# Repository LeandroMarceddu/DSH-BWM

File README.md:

# DSH-BWM
# DSH-BetterWaterManager
An attempt to make an RO-water unit a little bit more smart. 

PCB in boards/.

The rest is code.

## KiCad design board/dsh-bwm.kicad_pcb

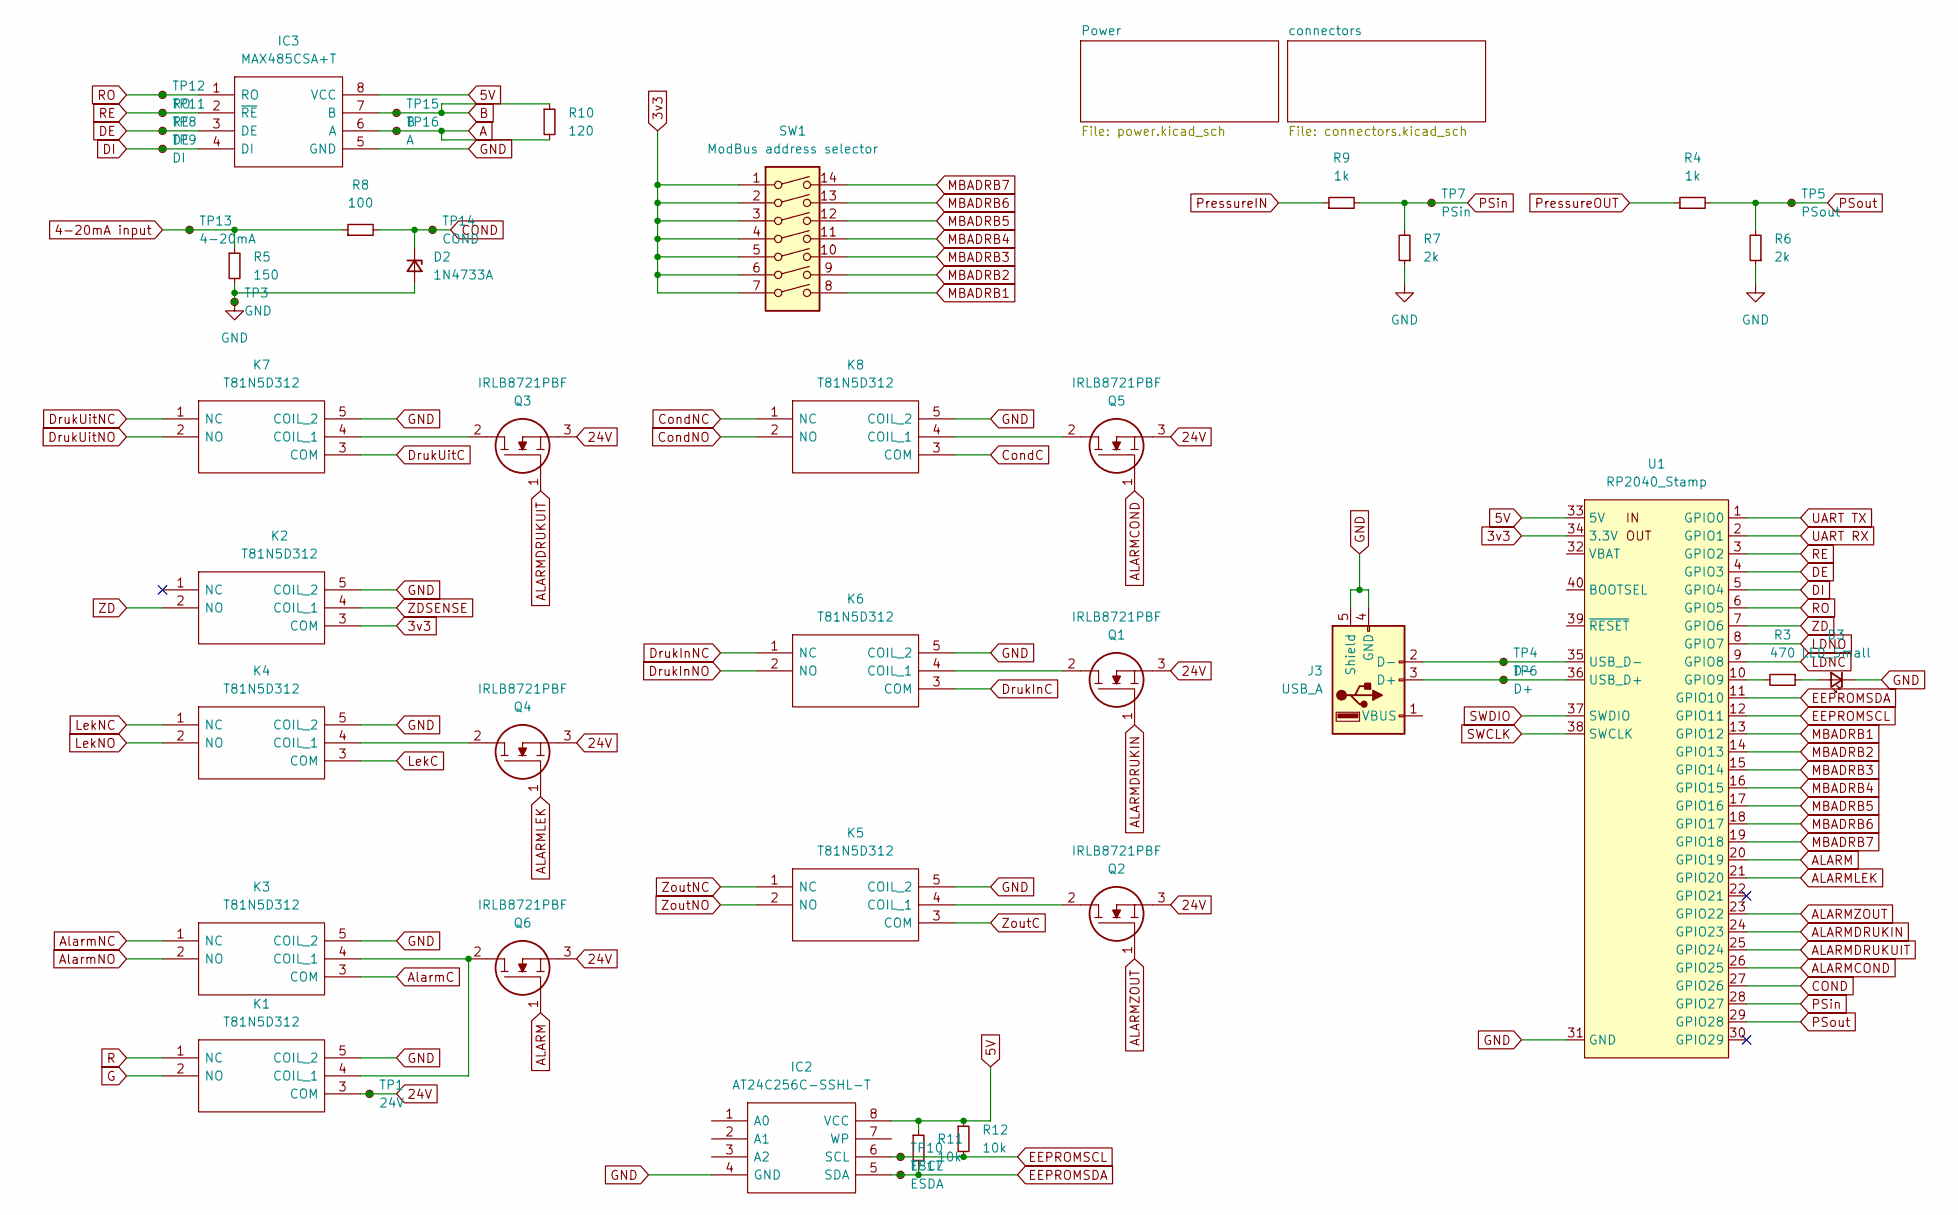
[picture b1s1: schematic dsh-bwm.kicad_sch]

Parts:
D2: 1N4733A; DIOAD1380W86L436D236
D3: LED_Small; LED_0603_1608Metric
IC2: AT24C256C-SSHL-T; SOIC127P600X175-8N; Manufacturer_Part_Number AT24C256C-SSHL-T; Mouser Part Number 556-AT24C256C-SSHL-T
IC3: MAX485CSA+T; SOIC127P600X175-8N; Manufacturer_Part_Number MAX485CSA+T; Mouser Part Number 700-MAX485CSAT
J3: USB_A; USB_A_Molex_105057_Vertical
K1, K2, K3, K4, K5, K6, K7, K8: T81N5D312; T81H5D31212; Manufacturer_Part_Number T81N5D312-05; Mouser Part Number 655-T81N5D312-05
Q1, Q2, Q3, Q4, Q5, Q6: IRLB8721PBF; TO254P483X1016X1994-3P; Manufacturer_Part_Number IRLB8721PBF; Mouser Part Number 942-IRLB8721PBF
R3: 470; R_0805_2012Metric
R4, R9: 1k; R_0805_2012Metric
R5: 150; R_0805_2012Metric; JLC 0402WGF1500TCE
R6, R7: 2k; R_0805_2012Metric
R8: 100; R_0805_2012Metric
R10: 120; R_0805_2012Metric
R11, R12: 10k; R_0805_2012Metric; JLC 0402WGF1500TCE
SW1: ModBus address selector; SW_DIP_SPSTx07_Slide_6.7x19.34mm_W7.62mm_P2.54mm_LowProfile
TP1: 24V; TestPoint_Pad_D1.5mm
TP3: GND; TestPoint_Pad_D1.5mm
TP4: D-; TestPoint_Pad_D1.5mm
TP5: PSout; TestPoint_Pad_D1.5mm
TP6: D+; TestPoint_Pad_D1.5mm
TP7: PSin; TestPoint_Pad_D1.5mm
TP8: DE; TestPoint_Pad_D1.5mm
TP9: DI; TestPoint_Pad_D1.5mm
TP10: ESCL; TestPoint_Pad_D1.5mm
TP11: RE; TestPoint_Pad_D1.5mm
TP12: RO; TestPoint_Pad_D1.5mm
TP13: 4-20mA; TestPoint_Pad_D1.5mm
TP14: COND; TestPoint_Pad_D1.5mm
TP15: B; TestPoint_Pad_D1.5mm
TP16: A; TestPoint_Pad_D1.5mm
TP17: ESDA; TestPoint_Pad_D1.5mm
U1: RP2040_Stamp; RP2040_Stamp_SMD

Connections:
3v3: K2.3 (COM), SW1.1, SW1.2, SW1.3, SW1.4, SW1.5, SW1.6, SW1.7, U1.34 (3.3V); also elsewhere on the board
4-20mA input: R5.1, R8.1, TP13.1; also elsewhere on the board
5V: IC2.8 (VCC), IC3.8 (VCC), R11.1, R12.1, U1.33 (5V); also elsewhere on the board
24V: K1.3 (COM), Q1.3, Q2.3, Q3.3, Q4.3, Q5.3, Q6.3, TP1.1; also elsewhere on the board
A: IC3.6 (A), R10.2, TP16.1; also elsewhere on the board
ALARM: Q6.1, U1.20 (GPIO19)
ALARMCOND: Q5.1, U1.26 (GPIO25)
ALARMDRUKIN: Q1.1, U1.24 (GPIO23)
ALARMDRUKUIT: Q3.1, U1.25 (GPIO24)
ALARMLEK: Q4.1, U1.21 (GPIO20)
ALARMZOUT: Q2.1, U1.23 (GPIO22)
AlarmC: K3.3 (COM); also elsewhere on the board
AlarmNC: K3.1 (NC); also elsewhere on the board
AlarmNO: K3.2 (NO); also elsewhere on the board
B: IC3.7 (B), R10.1, TP15.1; also elsewhere on the board
COND: D2.1 (K), R8.2, TP14.1, U1.27 (GPIO26)
CondC: K8.3 (COM); also elsewhere on the board
CondNC: K8.1 (NC); also elsewhere on the board
CondNO: K8.2 (NO); also elsewhere on the board
DE: IC3.3 (DE), TP8.1, U1.4 (GPIO3)
DI: IC3.4 (DI), TP9.1, U1.5 (GPIO4)
DrukInC: K6.3 (COM); also elsewhere on the board
DrukInNC: K6.1 (NC); also elsewhere on the board
DrukInNO: K6.2 (NO); also elsewhere on the board
DrukUitC: K7.3 (COM); also elsewhere on the board
DrukUitNC: K7.1 (NC); also elsewhere on the board
DrukUitNO: K7.2 (NO); also elsewhere on the board
EEPROMSCL: IC2.6 (SCL), R12.2, TP10.1, U1.12 (GPIO11)
EEPROMSDA: IC2.5 (SDA), R11.2, TP17.1, U1.11 (GPIO10)
G: K1.2 (NO); also elsewhere on the board
GND: D2.2 (A), D3.1 (K), IC2.4 (GND), IC3.5 (GND), J3.4 (GND), J3.5 (Shield), K1.5 (COIL_2), K2.5 (COIL_2), K3.5 (COIL_2), K4.5 (COIL_2), K5.5 (COIL_2), K6.5 (COIL_2), K7.5 (COIL_2), K8.5 (COIL_2), R5.2, R6.1, R7.1, TP3.1, U1.31 (GND); also elsewhere on the board
LDNC: U1.9 (GPIO8); also elsewhere on the board
LDNO: U1.8 (GPIO7); also elsewhere on the board
LekC: K4.3 (COM); also elsewhere on the board
LekNC: K4.1 (NC); also elsewhere on the board
LekNO: K4.2 (NO); also elsewhere on the board
MBADRB1: SW1.8, U1.13 (GPIO12)
MBADRB2: SW1.9, U1.14 (GPIO13)
MBADRB3: SW1.10, U1.15 (GPIO14)
MBADRB4: SW1.11, U1.16 (GPIO15)
MBADRB5: SW1.12, U1.17 (GPIO16)
MBADRB6: SW1.13, U1.18 (GPIO17)
MBADRB7: SW1.14, U1.19 (GPIO18)
unnamed: D3.2 (A), R3.1
unnamed: J3.2 (D-), TP4.1, U1.35 (USB_D-)
unnamed: J3.3 (D+), TP6.1, U1.36 (USB_D+)
unnamed: K1.4 (COIL_1), K3.4 (COIL_1), Q6.2
unnamed: K4.4 (COIL_1), Q4.2
unnamed: K5.4 (COIL_1), Q2.2
unnamed: K6.4 (COIL_1), Q1.2
unnamed: K7.4 (COIL_1), Q3.2
unnamed: K8.4 (COIL_1), Q5.2
unnamed: R3.2, U1.10 (GPIO9)
PSin: R7.2, R9.2, TP7.1, U1.28 (GPIO27)
PSout: R4.2, R6.2, TP5.1, U1.29 (GPIO28)
PressureIN: R9.1; also elsewhere on the board
PressureOUT: R4.1; also elsewhere on the board
R: K1.1 (NC); also elsewhere on the board
RE: IC3.2 (~RE), TP11.1, U1.3 (GPIO2)
RO: IC3.1 (RO), TP12.1, U1.6 (GPIO5)
SWCLK: U1.38 (SWCLK); also elsewhere on the board
SWDIO: U1.37 (SWDIO); also elsewhere on the board
UART RX: U1.2 (GPIO1); also elsewhere on the board
UART TX: U1.1 (GPIO0); also elsewhere on the board
ZD: K2.2 (NO), U1.7 (GPIO6)
ZDSENSE: K2.4 (COIL_1); also elsewhere on the board
ZoutC: K5.3 (COM); also elsewhere on the board
ZoutNC: K5.1 (NC); also elsewhere on the board
ZoutNO: K5.2 (NO); also elsewhere on the board

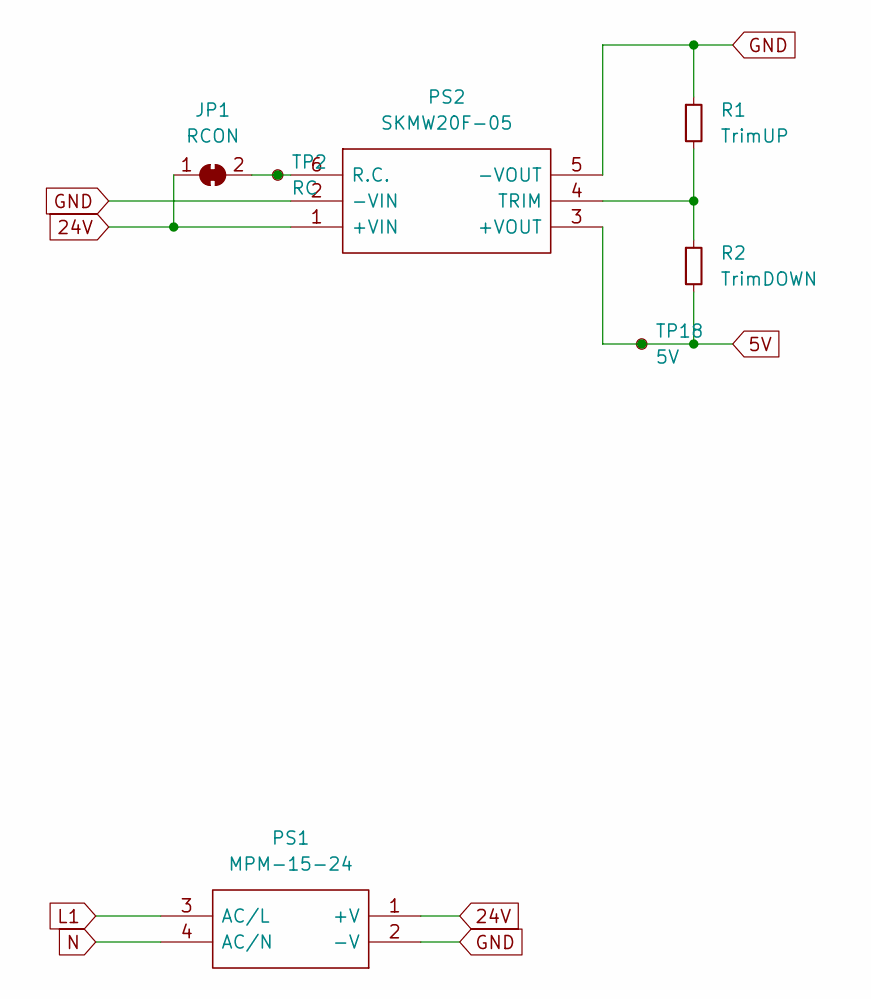
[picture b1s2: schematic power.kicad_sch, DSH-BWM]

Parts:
JP1: RCON; SolderJumper-2_P1.3mm_Open_RoundedPad1.0x1.5mm
PS1: MPM-15-24; MPM1524; Manufacturer_Part_Number MPM-15-24; Mouser Part Number 709-MPM-15-24
PS2: SKMW20F-05; SKMW20F05; Manufacturer_Part_Number SKMW20F-05; Mouser Part Number 709-SKMW20F-05
R1: TrimUP; R_0805_2012Metric
R2: TrimDOWN; R_0805_2012Metric
TP2: RC; TestPoint_Pad_D1.5mm
TP18: 5V; TestPoint_Pad_D1.5mm

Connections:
5V: PS2.3 (+VOUT), R2.2, TP18.1; also elsewhere on the board
24V: JP1.1 (A), PS1.1 (+V), PS2.1 (+VIN); also elsewhere on the board
GND: PS1.2 (-V), PS2.2 (-VIN), PS2.5 (-VOUT), R1.1; also elsewhere on the board
L1: PS1.3 (AC/L); also elsewhere on the board
N: PS1.4 (AC/N); also elsewhere on the board
unnamed: PS2.4 (TRIM), R1.2, R2.1
unnamed: JP1.2 (B), PS2.6 (R.C.), TP2.1

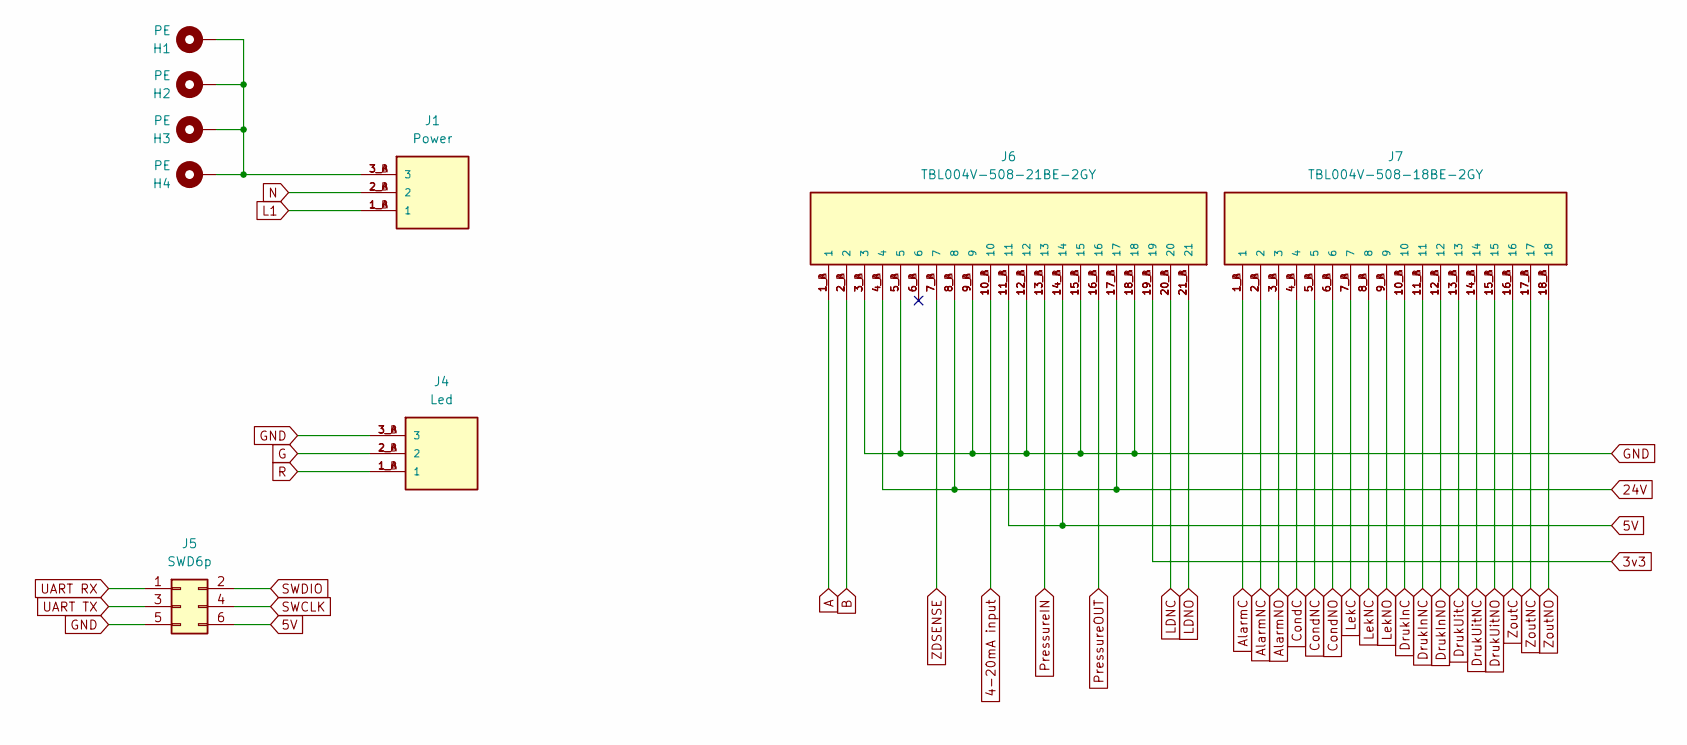
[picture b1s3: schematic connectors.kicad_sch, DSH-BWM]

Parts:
H1, H2, H3, H4: PE; MountingHole_3mm_Pad
J1: Power; CUI_TBL004V-508-03BE-2GY
J4: Led; CUI_TBL004V-508-03BE-2GY
J5: SWD6p; PinHeader_2x03_P2.54mm_Vertical
J6: TBL004V-508-21BE-2GY; CUI_TBL004V-508-21BE-2GY
J7: TBL004V-508-18BE-2GY; CUI_TBL004V-508-18BE-2GY

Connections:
3v3: J6.19_A (19), J6.19_B (19); also elsewhere on the board
4-20mA input: J6.10_A (10), J6.10_B (10); also elsewhere on the board
5V: J5.6, J6.11_A (11), J6.11_B (11), J6.14_A (14), J6.14_B (14); also elsewhere on the board
24V: J6.4_A (4), J6.4_B (4), J6.8_A (8), J6.8_B (8), J6.17_A (17), J6.17_B (17); also elsewhere on the board
A: J6.1_A (1), J6.1_B (1); also elsewhere on the board
AlarmC: J7.1_A (1), J7.1_B (1); also elsewhere on the board
AlarmNC: J7.2_A (2), J7.2_B (2); also elsewhere on the board
AlarmNO: J7.3_A (3), J7.3_B (3); also elsewhere on the board
B: J6.2_A (2), J6.2_B (2); also elsewhere on the board
CondC: J7.4_A (4), J7.4_B (4); also elsewhere on the board
CondNC: J7.5_A (5), J7.5_B (5); also elsewhere on the board
CondNO: J7.6_A (6), J7.6_B (6); also elsewhere on the board
DrukInC: J7.10_A (10), J7.10_B (10); also elsewhere on the board
DrukInNC: J7.11_A (11), J7.11_B (11); also elsewhere on the board
DrukInNO: J7.12_A (12), J7.12_B (12); also elsewhere on the board
DrukUitC: J7.13_A (13), J7.13_B (13); also elsewhere on the board
DrukUitNC: J7.14_A (14), J7.14_B (14); also elsewhere on the board
DrukUitNO: J7.15_A (15), J7.15_B (15); also elsewhere on the board
G: J4.2_A (2), J4.2_B (2); also elsewhere on the board
GND: J4.3_A (3), J4.3_B (3), J5.5, J6.3_A (3), J6.3_B (3), J6.5_A (5), J6.5_B (5), J6.9_A (9), J6.9_B (9), J6.12_A (12), J6.12_B (12), J6.15_A (15), J6.15_B (15), J6.18_A (18), J6.18_B (18); also elsewhere on the board
L1: J1.1_A (1), J1.1_B (1); also elsewhere on the board
LDNC: J6.20_A (20), J6.20_B (20); also elsewhere on the board
LDNO: J6.21_A (21), J6.21_B (21); also elsewhere on the board
LekC: J7.7_A (7), J7.7_B (7); also elsewhere on the board
LekNC: J7.8_A (8), J7.8_B (8); also elsewhere on the board
LekNO: J7.9_A (9), J7.9_B (9); also elsewhere on the board
N: J1.2_A (2), J1.2_B (2); also elsewhere on the board
unnamed: H1.1, H2.1, H3.1, H4.1, J1.3_A (3), J1.3_B (3)
PressureIN: J6.13_A (13), J6.13_B (13); also elsewhere on the board
PressureOUT: J6.16_A (16), J6.16_B (16); also elsewhere on the board
R: J4.1_A (1), J4.1_B (1); also elsewhere on the board
SWCLK: J5.4; also elsewhere on the board
SWDIO: J5.2; also elsewhere on the board
UART RX: J5.1; also elsewhere on the board
UART TX: J5.3; also elsewhere on the board
ZDSENSE: J6.7_A (7), J6.7_B (7); also elsewhere on the board
ZoutC: J7.16_A (16), J7.16_B (16); also elsewhere on the board
ZoutNC: J7.17_A (17), J7.17_B (17); also elsewhere on the board
ZoutNO: J7.18_A (18), J7.18_B (18); also elsewhere on the board

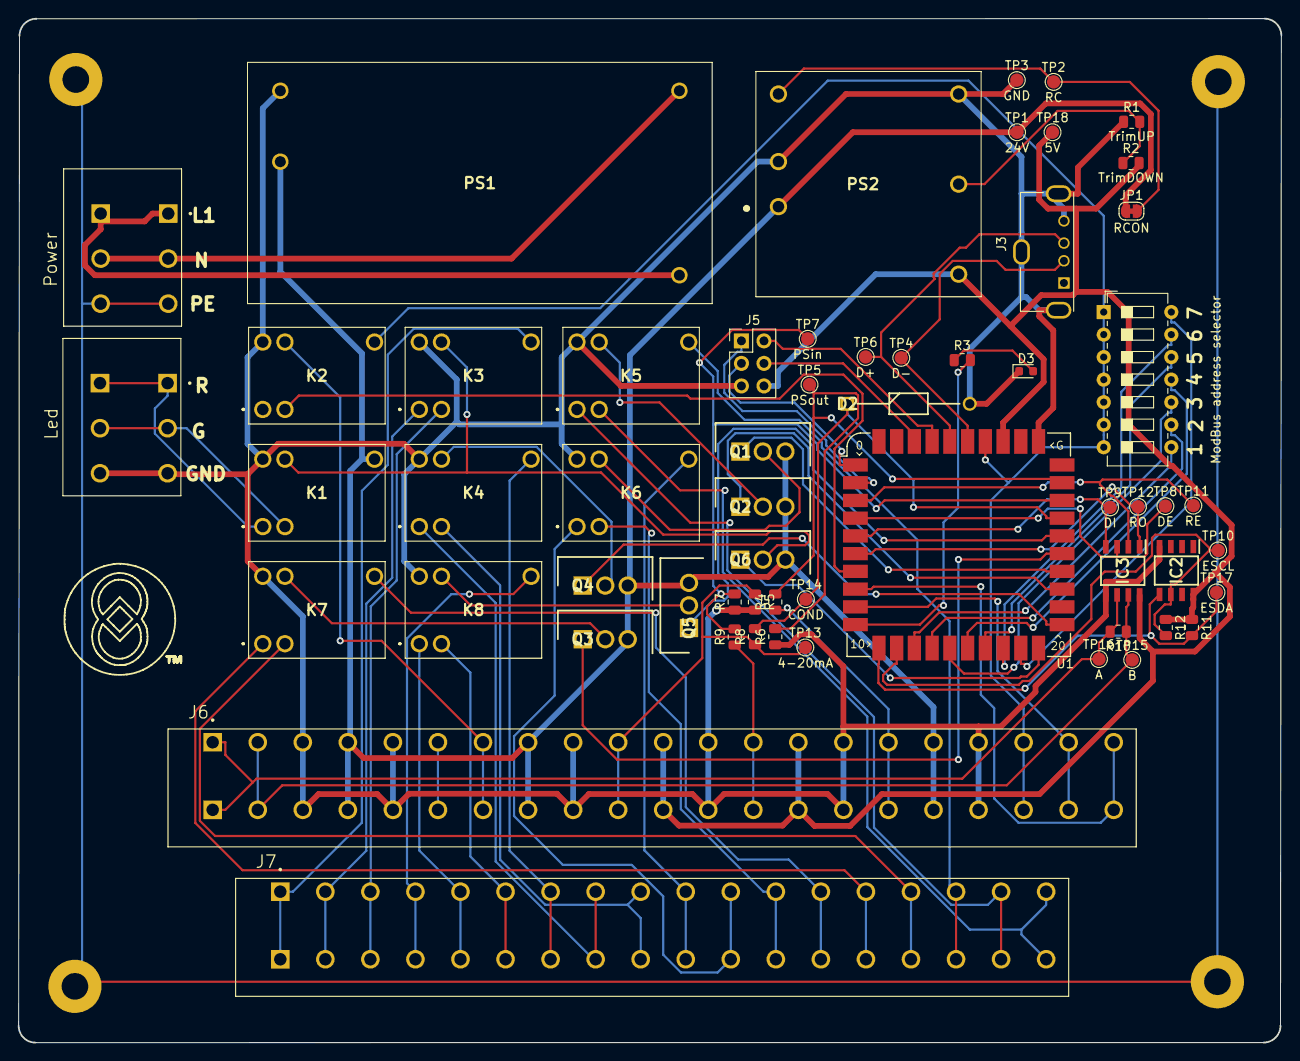
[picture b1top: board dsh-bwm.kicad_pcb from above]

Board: 2 copper layers, 142.4 x 115.5 mm, 63 parts (0 on the bottom side), 74 nets.

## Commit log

2022-12-04 Redo traces - MPS fixes
2022-12-04 Traces, traces everywhere
2022-12-04 Bigger is better?
2022-12-05 Fix unrouted, thanks Emiel
2022-12-05 RP2040 Stamp
2022-12-10 Power shit and copper fillz boi
2022-12-19 board update, modbus address selector
2022-12-26 TPs, vias, some comments on board, fml
2023-02-13 pushpushpush
